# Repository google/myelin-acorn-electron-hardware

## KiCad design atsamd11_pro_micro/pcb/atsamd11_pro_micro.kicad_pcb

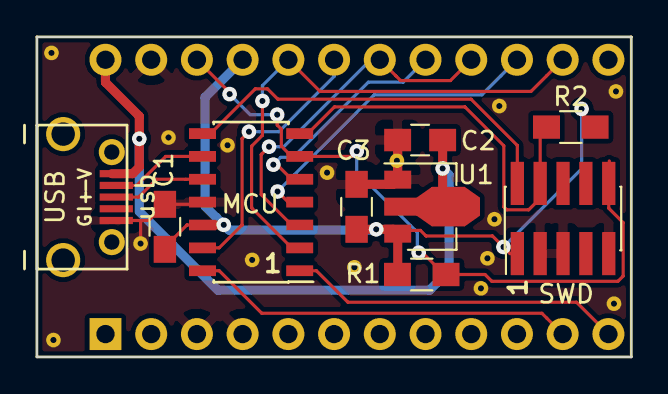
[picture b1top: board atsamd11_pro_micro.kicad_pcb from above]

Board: 2 copper layers, 33.0 x 17.8 mm, 25 parts (0 on the bottom side), 15 nets.

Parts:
C1: 100n; C_0805_HandSoldering
C2, C3: 1u; C_0805_HandSoldering
MCU: atsamd11c; SOIC-14_3.9x8.7mm_Pitch1.27mm
PRO: Pro Micro 5V; pro_micro
R1: 10k; R_0805_HandSoldering
R2: 1k; R_0805_HandSoldering
SWD: swd; Pin_Header_Straight_2x05_Pitch1.27mm_SMD
U1: MCP1700T-3302E/MB; SOT-89-3
USB: usb; micro_usb_b_smd_molex
staple_single1, staple_single2, staple_single3, staple_single4, staple_single5, staple_single6, staple_single7, staple_single8, staple_single9, staple_single10, staple_single11, staple_single12, staple_single13, staple_single14, staple_single15: via_single

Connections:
3V3: C1.2, C3.1, MCU.12, PRO.21, R1.2, R2.2, SWD.1, U1.3
5V: C2.2, PRO.24, U1.2, USB.1
GND: C1.1, C2.1, C3.2, MCU.11, PRO.3, PRO.4, PRO.23, SWD.3, SWD.5, SWD.9, U1.1, USB.5, staple_single1.1, staple_single2.1, staple_single3.1, staple_single4.1, staple_single5.1, staple_single6.1, staple_single7.1, staple_single8.1, staple_single9.1, staple_single10.1, staple_single11.1, staple_single12.1, staple_single13.1, staple_single14.1, staple_single15.1
SWCLK: MCU.7, R2.1, SWD.4
SWDIO: MCU.8, SWD.2
USBDM: MCU.9, USB.2
USBDP: MCU.10, USB.3
mcu_GPIO_D8: MCU.14, PRO.11
mcu_GPIO_D18: MCU.5, PRO.17
mcu_GPIO_D20: MCU.13, PRO.19
mcu_MISO: MCU.4, PRO.15
mcu_MOSI_TDI: MCU.2, PRO.14, PRO.20
mcu_RESET: MCU.6, PRO.22, R1.1, SWD.10
mcu_SCK_TMS: MCU.3, PRO.16, PRO.18
mcu_SS: MCU.1, PRO.12

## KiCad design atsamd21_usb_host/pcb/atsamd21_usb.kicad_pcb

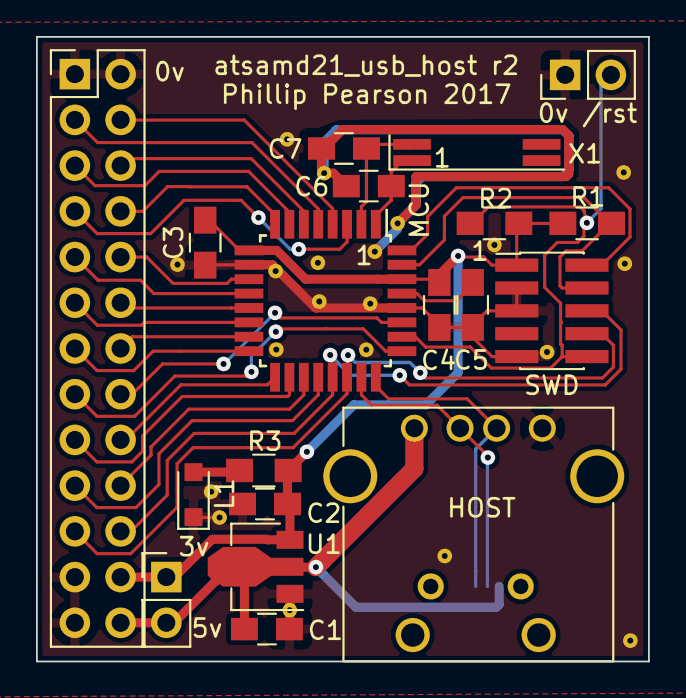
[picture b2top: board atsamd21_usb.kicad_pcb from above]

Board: 2 copper layers, 34.0 x 34.7 mm, 40 parts (1 on the bottom side), 32 nets.

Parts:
C1, C2, C5: 1u; C_0805_HandSoldering
C3, C4: 100n; C_0805_HandSoldering
C6, C7: 15p; C_0805_HandSoldering
CON: pins; Pin_Header_Straight_2x13_Pitch2.54mm
HOST: usb host; USB_A
L1: led; D_SOD-323_HandSoldering
MCU: ATSAMD21E18A; TQFP-32_7x7mm_Pitch0.8mm
PWR: reset; Pin_Header_Straight_1x02_Pitch2.54mm
R1: 10k; R_0805_HandSoldering
R2: 1k; R_0805_HandSoldering
R3: 330R; R_0805_HandSoldering
RST: reset; Pin_Header_Straight_1x02_Pitch2.54mm
SWD: swd; Pin_Header_Straight_2x05_Pitch1.27mm_SMD
U1: MCP1700T-3302E/MB; SOT-89-3
USB: usb; micro_usb_b_smd_molex
X1: MC146 32768Hz; Crystal_SMD_SeikoEpson_MC146-4pin_6.7x1.5mm_HandSoldering
staple_single1, staple_single2, staple_single3, staple_single4, staple_single5, staple_single6, staple_single7, staple_single8, staple_single9, staple_single10, staple_single11, staple_single12, staple_single13, staple_single14, staple_single15, staple_single16, staple_single17, staple_single18, staple_single19, staple_single20: via_single

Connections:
3V3: C2.1, C3.2, C4.2, CON.24, MCU.9, MCU.30, PWR.1, R1.2, R2.2, R3.1, SWD.1, U1.3
5V: C1.2, CON.26, HOST.1, PWR.2, U1.2, USB.1
GND: C1.1, C2.2, C3.1, C4.1, C5.1, C6.1, C7.1, CON.1, CON.2, CON.23, CON.25, HOST.4, L1.1, MCU.10, MCU.28, RST.1, SWD.3, SWD.5, SWD.9, U1.1, USB.5, staple_single1.1, staple_single2.1, staple_single3.1, staple_single4.1, staple_single5.1, staple_single6.1, staple_single7.1, staple_single8.1, staple_single9.1, staple_single10.1, staple_single11.1, staple_single12.1, staple_single13.1, staple_single14.1, staple_single15.1, staple_single16.1, staple_single17.1, staple_single18.1, staple_single19.1, staple_single20.1
PA02: CON.7, MCU.3
PA03: CON.4, MCU.4
PA04: CON.3, MCU.5
PA05: CON.6, MCU.6
PA06: CON.5, MCU.7
PA07: CON.8, MCU.8
PA08: CON.10, MCU.11
PA09: CON.9, MCU.12
PA10: CON.12, MCU.13
PA11: CON.11, MCU.14
PA14: CON.14, MCU.15
PA15: CON.13, MCU.16
PA16: CON.18, MCU.17
PA17: CON.17, MCU.18
PA18: CON.20, MCU.19
PA19: CON.19, MCU.20
PA27: CON.15, MCU.25
PA28: CON.16, MCU.27
SWCLK: MCU.31, R2.1, SWD.4
SWDIO: MCU.32, SWD.2
USBDM: HOST.2, MCU.23, USB.2
USBDP: HOST.3, MCU.24, USB.3
VDDCORE: C5.2, MCU.29
XTAL_IN: C6.2, MCU.1, X1.1
XTAL_OUT: C7.2, MCU.2, X1.4
mcu_RESET: MCU.26, R1.1, RST.2, SWD.10
mcu_RXD: CON.21, MCU.22, SWD.8
mcu_TXD: CON.22, MCU.21, SWD.6
power_led_anode: L1.2, R3.2

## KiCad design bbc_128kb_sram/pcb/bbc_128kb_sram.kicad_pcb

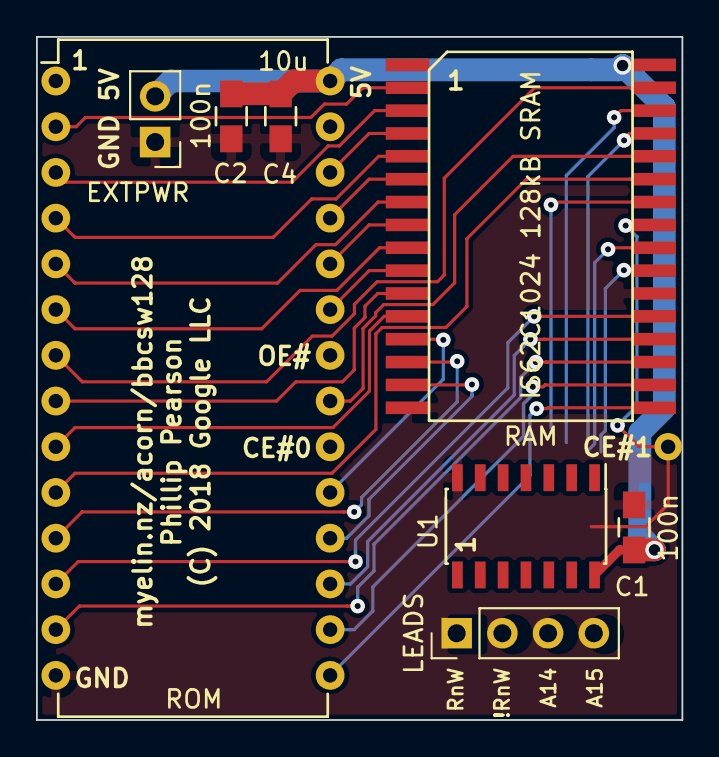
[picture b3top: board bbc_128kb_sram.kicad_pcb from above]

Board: 2 copper layers, 35.9 x 38.0 mm, 10 parts (1 on the bottom side), 30 nets.

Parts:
C1, C2, C3: 100n; C_0805_HandSoldering
C4: 10u; C_0805_HandSoldering
CS1: pin_32_60mil
EXTPWR: ext pwr; Pin_Header_Straight_1x02_Pitch2.54mm
LEADS: flying leads; Pin_Header_Straight_1x04_Pitch2.54mm
RAM: IS62C1024 128kB SRAM; issi_32l_450mil_sop
ROM: ROM chip; DIP-28_W15.24mm
U1: 74HCT00; SOIC-14_3.9x8.7mm_Pitch1.27mm

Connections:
5V: C1.1, C2.1, C3.1, C4.1, EXTPWR.2, RAM.32, ROM.28, U1.14
A0: RAM.27, ROM.10
A1: RAM.12, ROM.9
A2: RAM.11, ROM.8
A3: RAM.31, ROM.7
A4: RAM.9, ROM.6
A5: RAM.7, ROM.5
A6: RAM.5, ROM.4
A7: RAM.3, ROM.3
A8: RAM.6, ROM.25
A9: RAM.8, ROM.24
A10: RAM.28, ROM.21
A11: RAM.10, ROM.23
A12: RAM.2, ROM.2
A13: RAM.4, ROM.26
A14: LEADS.3, RAM.26
A15: LEADS.4, RAM.23
D0: RAM.14, ROM.11
D1: RAM.21, ROM.12
D2: RAM.19, ROM.13
D3: RAM.17, ROM.15
D4: RAM.18, ROM.16
D5: RAM.20, ROM.17
D6: RAM.15, ROM.18
D7: RAM.13, ROM.19
GND: C1.2, C2.2, C3.2, C4.2, EXTPWR.1, RAM.16, RAM.22, ROM.14, U1.7
bbc_n2MHzE: ROM.22, U1.1, U1.2
bbc_nCS0: ROM.20, U1.12
bbc_nCS1: CS1.1, RAM.25, U1.13
bbc_nn2MHzE: U1.3, U1.4, U1.9

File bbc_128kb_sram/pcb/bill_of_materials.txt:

Identifier	Value	Description	KiCad package
C1	100n	100n capacitor in 0805 package	Capacitors_SMD:C_0805_HandSoldering
C2	100n	100n capacitor in 0805 package	Capacitors_SMD:C_0805_HandSoldering
C3	100n	100n capacitor in 0805 package	Capacitors_SMD:C_0805_HandSoldering
C4	10u	10u capacitor in 0805 package	Capacitors_SMD:C_0805_HandSoldering
CS1			myelin-kicad:pin_32_60mil
EXTPWR	ext pwr	1x2 0.1 inch male header	Pin_Headers:Pin_Header_Straight_1x02_Pitch2.54mm
LEADS	flying leads	1x4 0.1 inch male header	Pin_Headers:Pin_Header_Straight_1x04_Pitch2.54mm
RAM	IS62C1024 128kB SRAM		myelin-kicad:issi_32l_450mil_sop
ROM	ROM chip	Adapter to emulate a 600mil 28-pin DIP, e.g. Digikey 1175-1525-5-ND	Housings_DIP:DIP-28_W15.24mm
U1	74HCT00		Housings_SOIC:SOIC-14_3.9x8.7mm_Pitch1.27mm

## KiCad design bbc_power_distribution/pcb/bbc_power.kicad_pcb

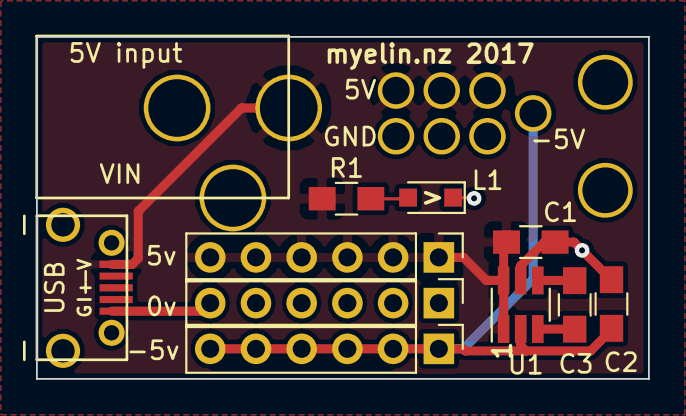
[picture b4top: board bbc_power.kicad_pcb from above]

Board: 2 copper layers, 34.0 x 19.0 mm, 20 parts (0 on the bottom side), 6 nets.

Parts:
C1, C2: 10u; R_0805_HandSoldering
C3: 1u; R_0805_HandSoldering
EXT5V: 5v; Pin_Header_Straight_1x06_Pitch2.54mm
EXT-5V: -5v; Pin_Header_Straight_1x06_Pitch2.54mm
EXTGND: 0v; Pin_Header_Straight_1x06_Pitch2.54mm
L1: led; D_SOD-323_HandSoldering
M1, M2: hole; pin_100_120mil
P1, P2, P3: 5V; pin_60mil
P4, P5, P6: GND; pin_60mil
P7: -5V; pin_60mil
R1: 330R; R_0805_HandSoldering
U1: Charge pump; SOT-23-6_Handsoldering
USB: usb; micro_usb_b_smd_molex
VIN: 5V input; dc10a_barrel_jack

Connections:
5V: C1.1, EXT5V.1, EXT5V.2, EXT5V.3, EXT5V.4, EXT5V.5, EXT5V.6, P1.1, P2.1, P3.1, R1.1, U1.1, U1.6, USB.1, VIN.TIP
-5V: C2.1, EXT-5V.1, EXT-5V.2, EXT-5V.3, EXT-5V.4, EXT-5V.5, EXT-5V.6, P7.1, U1.2
Cfly_minus: C3.2, U1.4
Cfly_plus: C3.1, U1.3
GND: C1.2, C2.2, EXTGND.1, EXTGND.2, EXTGND.3, EXTGND.4, EXTGND.5, EXTGND.6, L1.1, P4.1, P5.1, P6.1, U1.5, USB.5, VIN.RING
power_led_anode: L1.2, R1.2

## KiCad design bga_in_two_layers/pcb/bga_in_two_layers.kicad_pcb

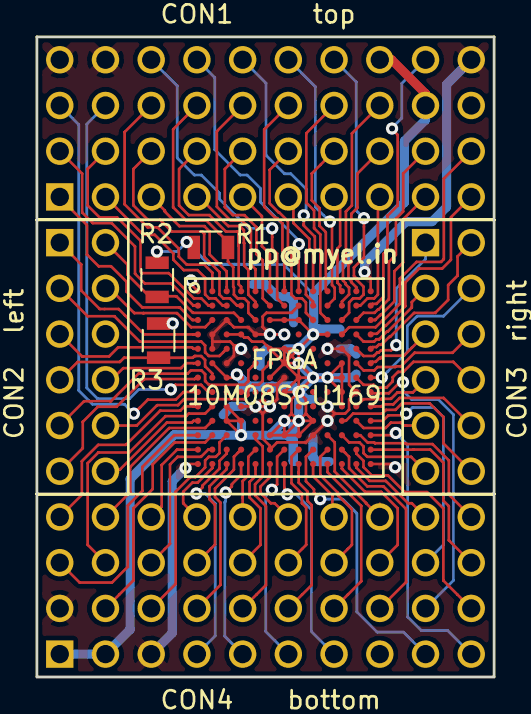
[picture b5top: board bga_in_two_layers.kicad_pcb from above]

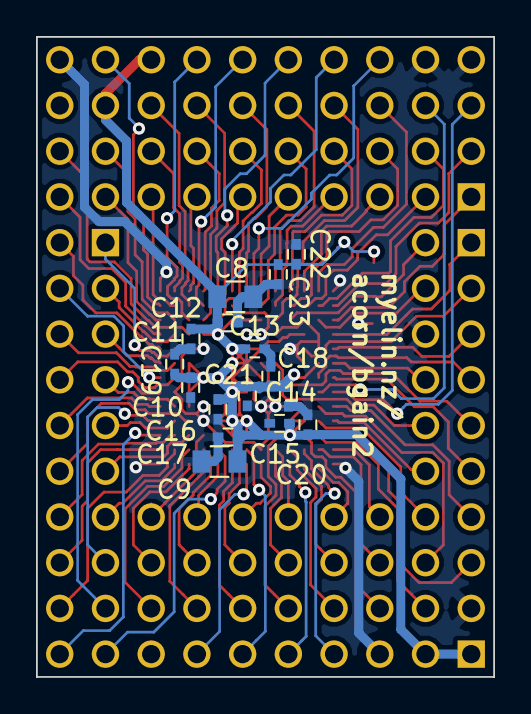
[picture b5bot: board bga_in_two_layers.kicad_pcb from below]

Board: 2 copper layers, 25.4 x 35.6 mm, 24 parts (16 on the bottom side), 94 nets.

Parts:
C8, C9: 1u; C_0805
C10, C11, C12, C13, C14, C15, C16, C17, C18, C19, C20, C21, C22, C23: 100n; C_0402
CON1: top; header_4x10_100mil
CON2: left; header_2x06_100mil
CON3: right; header_2x06_100mil
CON4: bottom; header_4x10_100mil
FPGA: 10M08SCU169; lattice_ubga169_smallpads
R1, R2: 10k; R_0805
R3: 1-10k; R_0805

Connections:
3V3: C8.1, C9.1, C10.1, C11.1, C12.1, C13.1, C14.1, C15.1, C16.1, C17.1, C18.1, C19.1, C20.1, C21.1, C22.1, C23.1, CON1.32, CON1.35, CON4.1, CON4.5, FPGA.C6, FPGA.C7, FPGA.C8, FPGA.D3, FPGA.D4, FPGA.D9, FPGA.D10, FPGA.E6, FPGA.E7, FPGA.E8, FPGA.F2, FPGA.F7, FPGA.F8, FPGA.F11, FPGA.G3, FPGA.G4, FPGA.G6, FPGA.G8, FPGA.G9, FPGA.G10, FPGA.G11, FPGA.H7, FPGA.H8, FPGA.H11, FPGA.J3, FPGA.J11, FPGA.K3, FPGA.K4, FPGA.K7, FPGA.K8, FPGA.K9, FPGA.L4, FPGA.L6, FPGA.L7, FPGA.L8, R1.2, R2.2
C1_1: CON1.1, FPGA.C1
C1_2: CON1.2, FPGA.B1
C1_3: CON1.3, FPGA.H1
C1_5: CON1.5, FPGA.B3
C1_6: CON1.6, FPGA.B2
C1_7: CON1.7, FPGA.H2
C1_9: CON1.9, FPGA.A3
C1_10: CON1.10, FPGA.B4
C1_11: CON1.11, FPGA.A2
C1_12: CON1.12, FPGA.B7
C1_13: CON1.13, FPGA.B5
C1_14: CON1.14, FPGA.A4
C1_16: CON1.16, FPGA.A8
C1_17: CON1.17, FPGA.A6
C1_18: CON1.18, FPGA.B6
C1_19: CON1.19, FPGA.A5
C1_20: CON1.20, FPGA.A9
C1_22: CON1.22, FPGA.C9
C1_23: CON1.23, FPGA.A7
C1_24: CON1.24, FPGA.B10
C1_25: CON1.25, FPGA.A11
C1_26: CON1.26, FPGA.A10
C1_27: CON1.27, FPGA.C10
C1_28: CON1.28, FPGA.C11
C1_29: CON1.29, FPGA.B12
C1_30: CON1.30, FPGA.A12
C1_31: CON1.31, FPGA.B11
C1_33: CON1.33, FPGA.C13
C1_34: CON1.34, FPGA.C12
C1_36: CON1.36, FPGA.B13
C1_37: CON1.37, FPGA.D13
C1_38: CON1.38, FPGA.D11
C2_1: CON2.1, FPGA.D1
C2_3: CON2.3, FPGA.E3
C2_4: CON2.4, FPGA.C2
C2_5: CON2.5, FPGA.E1
C2_8: CON2.8, FPGA.F1
C2_12: CON2.12, FPGA.K1
C3_1: CON3.1, FPGA.E12
C3_2_CLK3n: CON3.2, FPGA.E13
C3_3: CON3.3, FPGA.D12
C3_4: CON3.4, FPGA.G13
C3_5_CLK3p: CON3.5, FPGA.F13
C3_6: CON3.6, FPGA.F12
C3_7: CON3.7, FPGA.J12
C3_8: CON3.8, FPGA.G12
C3_9: CON3.9, FPGA.K12
C3_10: CON3.10, FPGA.J13
C3_11: CON3.11, FPGA.L11
C3_12: CON3.12, FPGA.K11
C4_3_VREFB2N0: CON4.3, FPGA.L1
C4_4: CON4.4, FPGA.J1
C4_6: CON4.6, FPGA.L2
C4_7: CON4.7, FPGA.J2
C4_8: CON4.8, FPGA.K2
C4_10: CON4.10, FPGA.L3
C4_11: CON4.11, FPGA.M2
C4_12: CON4.12, FPGA.M1
C4_13: CON4.13, FPGA.M3
C4_14: CON4.14, FPGA.M4
C4_15_DPCLK1: CON4.15, FPGA.N3
C4_16_DPCLK0: CON4.16, FPGA.N2
C4_17: CON4.17, FPGA.N4
C4_18: CON4.18, FPGA.L5
C4_19: CON4.19, FPGA.N5
C4_20: CON4.20, FPGA.M5
C4_21: CON4.21, FPGA.M7
C4_22: CON4.22, FPGA.N8
C4_23: CON4.23, FPGA.M8
C4_24: CON4.24, FPGA.N6
C4_25: CON4.25, FPGA.N7
C4_26: CON4.26, FPGA.N10
C4_27: CON4.27, FPGA.M10
C4_28: CON4.28, FPGA.N9
C4_30: CON4.30, FPGA.M11
C4_31: CON4.31, FPGA.N11
C4_32: CON4.32, FPGA.L10
C4_33: CON4.33, FPGA.M9
C4_34: CON4.34, FPGA.H13
C4_35: CON4.35, FPGA.K13
C4_36: CON4.36, FPGA.N12
C4_37: CON4.37, FPGA.L13
C4_38: CON4.38, FPGA.M12
C4_39: CON4.39, FPGA.M13
C4_40: CON4.40, FPGA.L12
GND: C8.2, C9.2, C10.2, C11.2, C12.2, C13.2, C14.2, C15.2, C16.2, C17.2, C18.2, C19.2, C20.2, C21.2, C22.2, C23.2, CON1.4, CON1.8, CON1.40, CON2.6, CON4.2, CON4.9, FPGA.A1, FPGA.A13, FPGA.B8, FPGA.C3, FPGA.D2, FPGA.D5, FPGA.D6, FPGA.D7, FPGA.E2, FPGA.E4, FPGA.E10, FPGA.E11, FPGA.F3, FPGA.G7, FPGA.H12, FPGA.J4, FPGA.J5, FPGA.J6, FPGA.J10, FPGA.K10, FPGA.L9, FPGA.M6, FPGA.N1, FPGA.N13, R3.2
fpga_CONF_DONE: CON1.15, FPGA.C5, R1.1
fpga_DEV_CLRn: CON1.21, FPGA.B9
fpga_TCK: CON2.7, FPGA.G2, R3.1
fpga_TDI: CON2.9, FPGA.F5
fpga_TDO: CON2.10, FPGA.F6
fpga_TMS: CON2.11, FPGA.G1
fpga_nSTATUS: CON2.2, FPGA.C4, R2.1

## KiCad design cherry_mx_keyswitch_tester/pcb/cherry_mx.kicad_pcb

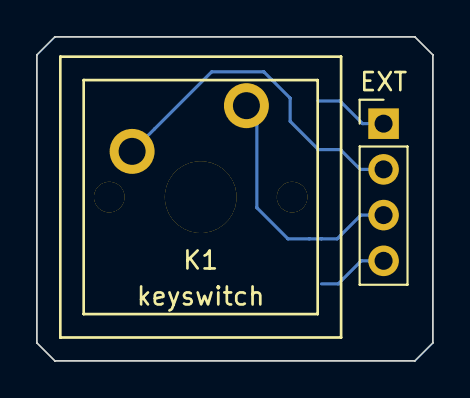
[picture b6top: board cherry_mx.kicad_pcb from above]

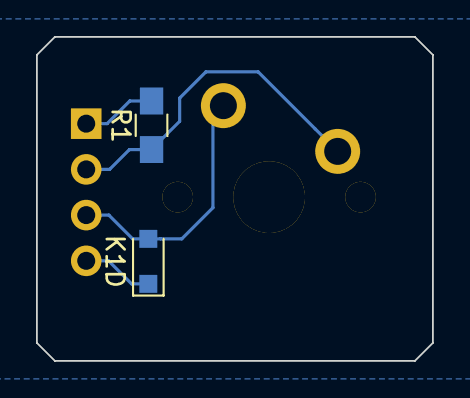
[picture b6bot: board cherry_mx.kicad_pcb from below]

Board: 2 copper layers, 22.0 x 18.0 mm, 4 parts (2 on the bottom side), 4 nets.

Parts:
EXT: ext; Pin_Header_Straight_1x04_Pitch2.54mm
K1: keyswitch; cherry_mx_pcb_mount
K1D: diode; D_SOD-323_HandSoldering
R1: 10k; R_0805_HandSoldering

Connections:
5V: EXT.1, R1.2
x: EXT.2, K1.1, R1.1
x_y_diode: EXT.3, K1.2, K1D.2
y: EXT.4, K1D.1

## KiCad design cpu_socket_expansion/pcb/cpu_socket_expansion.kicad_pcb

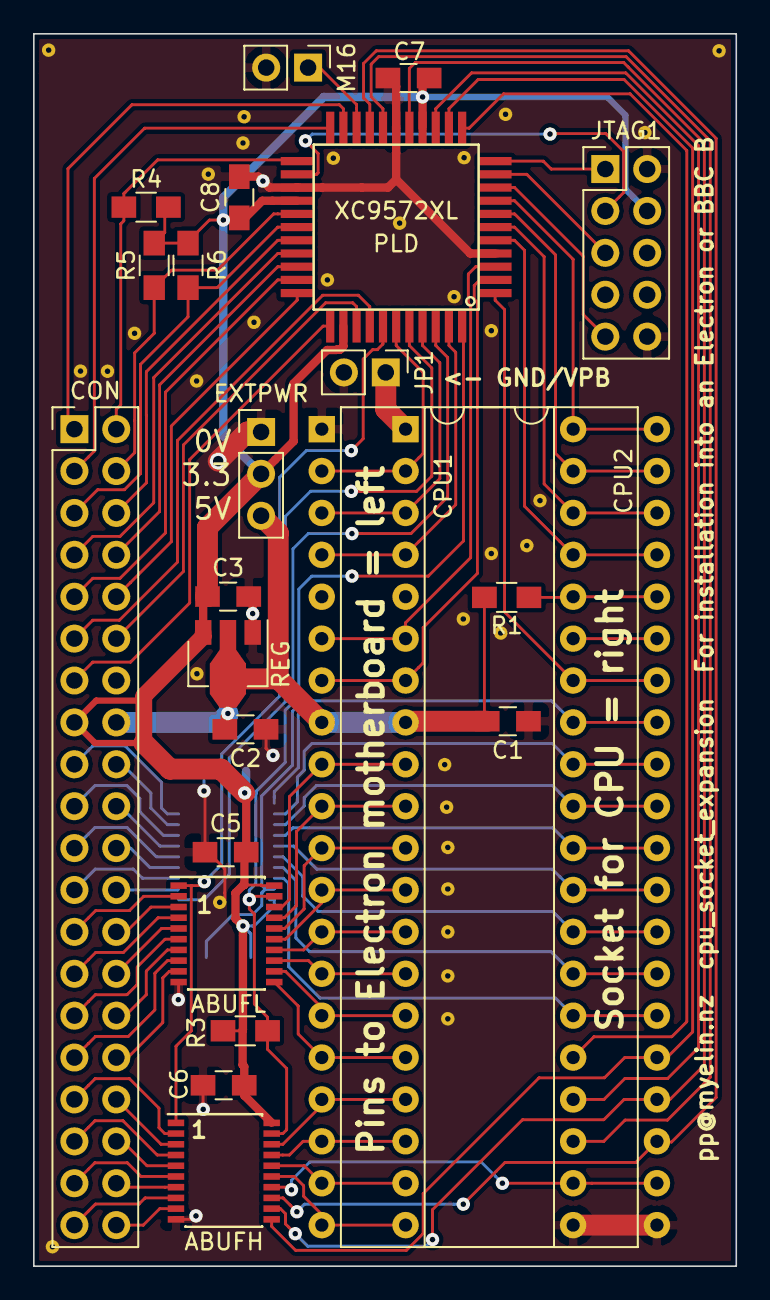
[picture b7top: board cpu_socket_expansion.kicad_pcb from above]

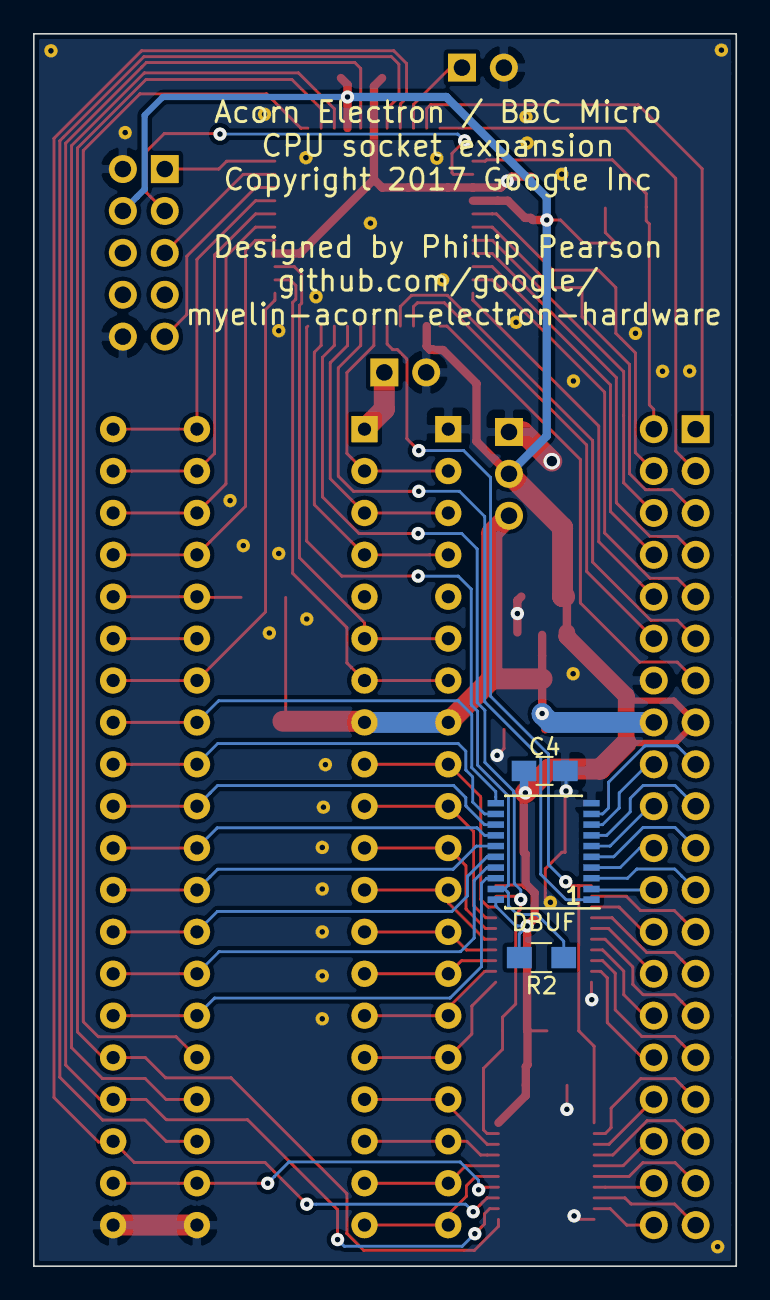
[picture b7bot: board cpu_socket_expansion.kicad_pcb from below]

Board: 2 copper layers, 42.6 x 74.7 mm, 59 parts (3 on the bottom side), 89 nets.

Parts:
ABUFH: 74LVC245; SSOP-20_4.4x6.5mm_Pitch0.65mm
ABUFL: 74LVC245; SSOP-20_4.4x6.5mm_Pitch0.65mm
C1, C4, C5, C6, C7, C8: 100n; C_0805_HandSoldering
C2, C3: 1u; C_0805_HandSoldering
CON: 2x20 connector for daughterboard; Pin_Header_Straight_2x20_Pitch2.54mm
CPU1, CPU2: 6502; DIP-40_W15.24mm
DBUF: 74LVC245; SSOP-20_4.4x6.5mm_Pitch0.65mm
EXTPWR: ext pwr; Pin_Header_Straight_1x03_Pitch2.54mm
JP1: VPB; Pin_Header_Straight_1x02_Pitch2.54mm
JTAG1: jtag; Pin_Header_Straight_2x05_Pitch2.54mm
M16: 16MHz; Pin_Header_Straight_1x02_Pitch2.54mm
PLD: XC9572XL; xilinx_vqg44
R1: 4k7; R_0805_HandSoldering
R2, R3, R4, R5, R6: 10k; R_0805_HandSoldering
REG: MCP1700T-3302E/MB; SOT-89-3
staple_single1, staple_single2, staple_single3, staple_single4, staple_single5, staple_single6, staple_single7, staple_single8, staple_single9, staple_single10, staple_single11, staple_single12, staple_single13, staple_single14, staple_single15, staple_single16, staple_single17, staple_single18, staple_single19, staple_single20, staple_single21, staple_single22, staple_single23, staple_single24, staple_single25, staple_single26, staple_single27, staple_single28, staple_single29, staple_single30, staple_single31, staple_single32, staple_single33: via_single

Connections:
3V3: ABUFH.20, ABUFL.20, C3.1, C4.2, C5.2, C6.2, C7.1, C8.1, CON.15, DBUF.20, EXTPWR.2, JTAG1.4, PLD.15, PLD.26, PLD.35, R2.2, R3.2, R4.2, R5.2, R6.2, REG.3
5V: C1.2, C2.2, CON.16, CPU1.8, CPU2.8, EXTPWR.3, R1.2, REG.2
16MHz: M16.1, PLD.20
GND: ABUFH.10, ABUFL.10, C1.1, C2.1, C3.2, C4.1, C5.1, C6.1, C7.2, C8.2, CON.14, CPU1.1, CPU1.21, CPU2.21, DBUF.10, EXTPWR.1, JP1.2, JTAG1.2, JTAG1.10, M16.2, PLD.4, PLD.17, PLD.25, REG.1, staple_single1.1, staple_single2.1, staple_single3.1, staple_single4.1, staple_single5.1, staple_single6.1, staple_single7.1, staple_single8.1, staple_single9.1, staple_single10.1, staple_single11.1, staple_single12.1, staple_single13.1, staple_single14.1, staple_single15.1, staple_single16.1, staple_single17.1, staple_single18.1, staple_single19.1, staple_single20.1, staple_single21.1, staple_single22.1, staple_single23.1, staple_single24.1, staple_single25.1, staple_single26.1, staple_single27.1, staple_single28.1, staple_single29.1, staple_single30.1, staple_single31.1, staple_single32.1, staple_single33.1
abuf_ext_to_cpu: ABUFH.1, ABUFL.1, PLD.38
abuf_nCE: ABUFH.19, ABUFL.19, PLD.42, R3.1
cpld_TCK: JTAG1.1, PLD.11
cpld_TDI: JTAG1.9, PLD.9
cpld_TDO: JTAG1.3, PLD.24
cpld_TMS: JTAG1.5, PLD.10
cpu_A0: ABUFL.18, CPU1.9, CPU2.9
cpu_A1: ABUFL.17, CPU1.10, CPU2.10
cpu_A2: ABUFL.16, CPU1.11, CPU2.11
cpu_A3: ABUFL.15, CPU1.12, CPU2.12
cpu_A4: ABUFL.14, CPU1.13, CPU2.13
cpu_A5: ABUFL.13, CPU1.14, CPU2.14
cpu_A6: ABUFL.12, CPU1.15, CPU2.15
cpu_A7: ABUFL.11, CPU1.16, CPU2.16
cpu_A8: ABUFH.18, CPU1.17, CPU2.17
cpu_A9: ABUFH.17, CPU1.18, CPU2.18
cpu_A10: ABUFH.16, CPU1.19, CPU2.19
cpu_A11: ABUFH.15, CPU1.20, CPU2.20
cpu_A12: ABUFH.14, CPU1.22, CPU2.22
cpu_A13_1: CPU1.23, PLD.18
cpu_A13_2: ABUFH.13, CPU2.23, PLD.19
cpu_A14_1: CPU1.24, PLD.14
cpu_A14_2: ABUFH.12, CPU2.24, PLD.16
cpu_A15_1: CPU1.25, PLD.12
cpu_A15_2: ABUFH.11, CPU2.25, PLD.13
cpu_D0: CPU1.33, CPU2.33, DBUF.11
cpu_D1: CPU1.32, CPU2.32, DBUF.12
cpu_D2: CPU1.31, CPU2.31, DBUF.13
cpu_D3: CPU1.30, CPU2.30, DBUF.14
cpu_D4: CPU1.29, CPU2.29, DBUF.15
cpu_D5: CPU1.28, CPU2.28, DBUF.16
cpu_D6: CPU1.27, CPU2.27, DBUF.17
cpu_D7: CPU1.26, CPU2.26, DBUF.18
cpu_GND_VPB_2: CPU2.1, JP1.1
cpu_NC_BE: CPU1.36, CPU2.36, R1.1
cpu_NC_XTLO: CPU1.35, CPU2.35
cpu_PHI0_IN: CPU1.37, CPU2.37, PLD.5
cpu_PHI1_OUT: CPU1.3, CPU2.3, PLD.41
cpu_PHI2_OUT: CPU1.39, CPU2.39, PLD.7
cpu_RDY: CPU1.2, CPU2.2, PLD.39
cpu_RnW: CPU1.34, CPU2.34, PLD.1
cpu_SYNC: CPU1.7, CPU2.7, PLD.2
cpu_nIRQ: CPU1.4, CPU2.4, PLD.43
cpu_nNMI: CPU1.6, CPU2.6, PLD.3
cpu_nRESET: CPU1.40, CPU2.40, PLD.8
cpu_nSO: CPU1.38, CPU2.38, PLD.6
dbuf_ext_to_cpu: DBUF.1, PLD.40
dbuf_nCE: DBUF.19, PLD.44, R2.1
ext_A0: ABUFL.2, CON.25
ext_A1: ABUFL.3, CON.26
ext_A2: ABUFL.4, CON.27
ext_A3: ABUFL.5, CON.28
ext_A4: ABUFL.6, CON.29
ext_A5: ABUFL.7, CON.30
ext_A6: ABUFL.8, CON.31
ext_A7: ABUFL.9, CON.32
ext_A8: ABUFH.2, CON.33
ext_A9: ABUFH.3, CON.34
ext_A10: ABUFH.4, CON.35
ext_A11: ABUFH.5, CON.36
ext_A12: ABUFH.6, CON.37
ext_A13: ABUFH.7, CON.38
ext_A14: ABUFH.8, CON.39
ext_A15: ABUFH.9, CON.40
ext_D0: CON.17, DBUF.9
ext_D1: CON.18, DBUF.8
ext_D2: CON.19, DBUF.7
ext_D3: CON.20, DBUF.6
ext_D4: CON.21, DBUF.5
ext_D5: CON.22, DBUF.4
ext_D6: CON.23, DBUF.3
ext_D7: CON.24, DBUF.2
ext_GP0: CON.1, PLD.21
ext_GP1: CON.2, PLD.23, R4.1
ext_GP2: CON.3, PLD.22
ext_GP3: CON.4, PLD.27, R5.1
ext_GP4: CON.5, PLD.28, R6.1
ext_GP5: CON.6, PLD.29
ext_GP6: CON.7, PLD.30
ext_GP7: CON.8, PLD.31
ext_GP8: CON.9, PLD.32
ext_GP9: CON.10, PLD.33
ext_GP10: CON.11, PLD.37
ext_GP11: CON.12, PLD.36
ext_GP12: CON.13, PLD.34

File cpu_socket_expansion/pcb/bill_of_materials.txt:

Identifier	Value	Description	KiCad package
ABUFH	74LVC245APW	74LVC245 in TSSOP20 with 4.4mm body width, e.g. Digikey 1727-3105-1-ND	Housings_SSOP:SSOP-20_4.4x6.5mm_Pitch0.65mm
ABUFL	74LVC245APW	74LVC245 in TSSOP20 with 4.4mm body width, e.g. Digikey 1727-3105-1-ND	Housings_SSOP:SSOP-20_4.4x6.5mm_Pitch0.65mm
C1	100n	100n capacitor in 0805 package	Capacitors_SMD:C_0805_HandSoldering
C2	1u	1u capacitor in 0805 package	Capacitors_SMD:C_0805_HandSoldering
C3	1u	1u capacitor in 0805 package	Capacitors_SMD:C_0805_HandSoldering
C4	100n	100n capacitor in 0805 package	Capacitors_SMD:C_0805_HandSoldering
C5	100n	100n capacitor in 0805 package	Capacitors_SMD:C_0805_HandSoldering
C6	100n	100n capacitor in 0805 package	Capacitors_SMD:C_0805_HandSoldering
C7	100n	100n capacitor in 0805 package	Capacitors_SMD:C_0805_HandSoldering
C8	100n	100n capacitor in 0805 package	Capacitors_SMD:C_0805_HandSoldering
CON	2x20 connector for daughterboard	2x20 0.1 inch male header	Pin_Headers:Pin_Header_Straight_2x20_Pitch2.54mm
CPU1	6502	adapter to emulate a 600mil 40-pin DIP, e.g. Digikey 1175-1527-5-ND	Housings_DIP:DIP-40_W15.24mm
CPU2	6502	600mil 40-pin DIP socket, e.g. Digikey 609-4716-ND	Housings_DIP:DIP-40_W15.24mm
DBUF	74LVC245APW	74LVC245 in TSSOP20 with 4.4mm body width, e.g. Digikey 1727-3105-1-ND	Housings_SSOP:SSOP-20_4.4x6.5mm_Pitch0.65mm
EXTPWR	ext pwr	1x3 0.1 inch male header	Pin_Headers:Pin_Header_Straight_1x03_Pitch2.54mm
JP1	VPB	1x2 0.1 inch male header	Pin_Headers:Pin_Header_Straight_1x02_Pitch2.54mm
JTAG1	jtag	2x5 header for JTAG programming.  Use generic 0.1 inch header strip or Digikey ED1543-ND.	Pin_Headers:Pin_Header_Straight_2x05_Pitch2.54mm
M16	16MHz	1x2 0.1 inch male header	Pin_Headers:Pin_Header_Straight_1x02_Pitch2.54mm
PLD	XC9572XL-10VQG44C	Xilinx XC9572XL in 44-pin 0.8mm TQFP package.  Any speed or temperature grade is OK.	myelin-kicad:xilinx_vqg44
R1	4k7	4k7 resistor in 0805 package	Resistors_SMD:R_0805_HandSoldering
R2	10k	10k resistor in 0805 package	Resistors_SMD:R_0805_HandSoldering
R3	10k	10k resistor in 0805 package	Resistors_SMD:R_0805_HandSoldering
R4	10k	10k resistor in 0805 package	Resistors_SMD:R_0805_HandSoldering
R5	10k	10k resistor in 0805 package	Resistors_SMD:R_0805_HandSoldering
R6	10k	10k resistor in 0805 package	Resistors_SMD:R_0805_HandSoldering
REG	MCP1700T-3302E/MB	3.3V LDO regulator, e.g. Digikey MCP1700T3302EMBCT-ND.  Search for the exact part number because there are many variants.	TO_SOT_Packages_SMD:SOT-89-3

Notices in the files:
atsamd11_pro_micro/pcb/atsamd11_pro_micro.kicad_pcb:
Copyright 2017 Google Inc
bbc_128kb_sram/pcb/bbc_128kb_sram.kicad_pcb:
(C) 2018 Google LLC
bbc_power_distribution/pcb/bbc_power.kicad_pcb:
(C) 2017 Google LLC
